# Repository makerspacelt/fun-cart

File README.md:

fun-cart
========

Electric drift cart

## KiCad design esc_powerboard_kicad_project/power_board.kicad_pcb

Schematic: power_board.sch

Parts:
C1, C2, C3, C4, C5, C6, C7, C8, C9, C10, C11, C12, C13, C14, C15, C16, C17, C18, C19, C20: 470u
GS1, GS2, GS3, GS4, GS5, GS6, GS7, GS8, GS9, GS10, GS11, GS12, GS13, GS14, GS15, GS16, GS17, GS18, GS19, GS20: GS2
P1: B+
P2: M-
P3: B-
P4, P5, P6, P7, P8: MOUNT_HOLE
Q1, Q2, Q3, Q4, Q5, Q6, Q7, Q8, Q9, Q10, Q11, Q12, Q13, Q14, Q15, Q16, Q17, Q18, Q19, Q20: IRFB7437PBF; TO220

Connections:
+24V: C1.1, C2.1, C3.1, C4.1, C5.1, C6.1, C7.1, C8.1, C9.1, C10.1, C11.1, C12.1, C13.1, C14.1, C15.1, C16.1, C17.1, C18.1, C19.1, C20.1, GS1.1 (G1), GS2.1 (G1), GS3.1 (G1), GS4.1 (G1), GS5.1 (G1), GS6.1 (G1), GS7.1 (G1), GS8.1 (G1), GS9.1 (G1), GS10.1 (G1), GS11.2 (G2), GS12.2 (G2), GS13.2 (G2), GS14.2 (G2), GS15.2 (G2), GS16.2 (G2), GS17.2 (G2), GS18.2 (G2), GS19.2 (G2), GS20.2 (G2), P1.1, Q1.D, Q3.D, Q5.D, Q7.D, Q9.D, Q11.D, Q13.D, Q15.D, Q17.D, Q19.D
/M-: P2.1, P4.1, P5.1, P6.1, P7.1, P8.1, Q1.S, Q2.D, Q3.S, Q4.D, Q5.S, Q6.D, Q7.S, Q8.D, Q9.S, Q10.D, Q11.S, Q12.D, Q13.S, Q14.D, Q15.S, Q16.D, Q17.S, Q18.D, Q19.S, Q20.D
GND: C1.2, C2.2, C3.2, C4.2, C5.2, C6.2, C7.2, C8.2, C9.2, C10.2, C11.2, C12.2, C13.2, C14.2, C15.2, C16.2, C17.2, C18.2, C19.2, C20.2, GS1.2 (G2), GS2.2 (G2), GS3.2 (G2), GS4.2 (G2), GS5.2 (G2), GS6.2 (G2), GS7.2 (G2), GS8.2 (G2), GS9.2 (G2), GS10.2 (G2), GS11.1 (G1), GS12.1 (G1), GS13.1 (G1), GS14.1 (G1), GS15.1 (G1), GS16.1 (G1), GS17.1 (G1), GS18.1 (G1), GS19.1 (G1), GS20.1 (G1), P3.1, Q2.S, Q4.S, Q6.S, Q8.S, Q10.S, Q12.S, Q14.S, Q16.S, Q18.S, Q20.S

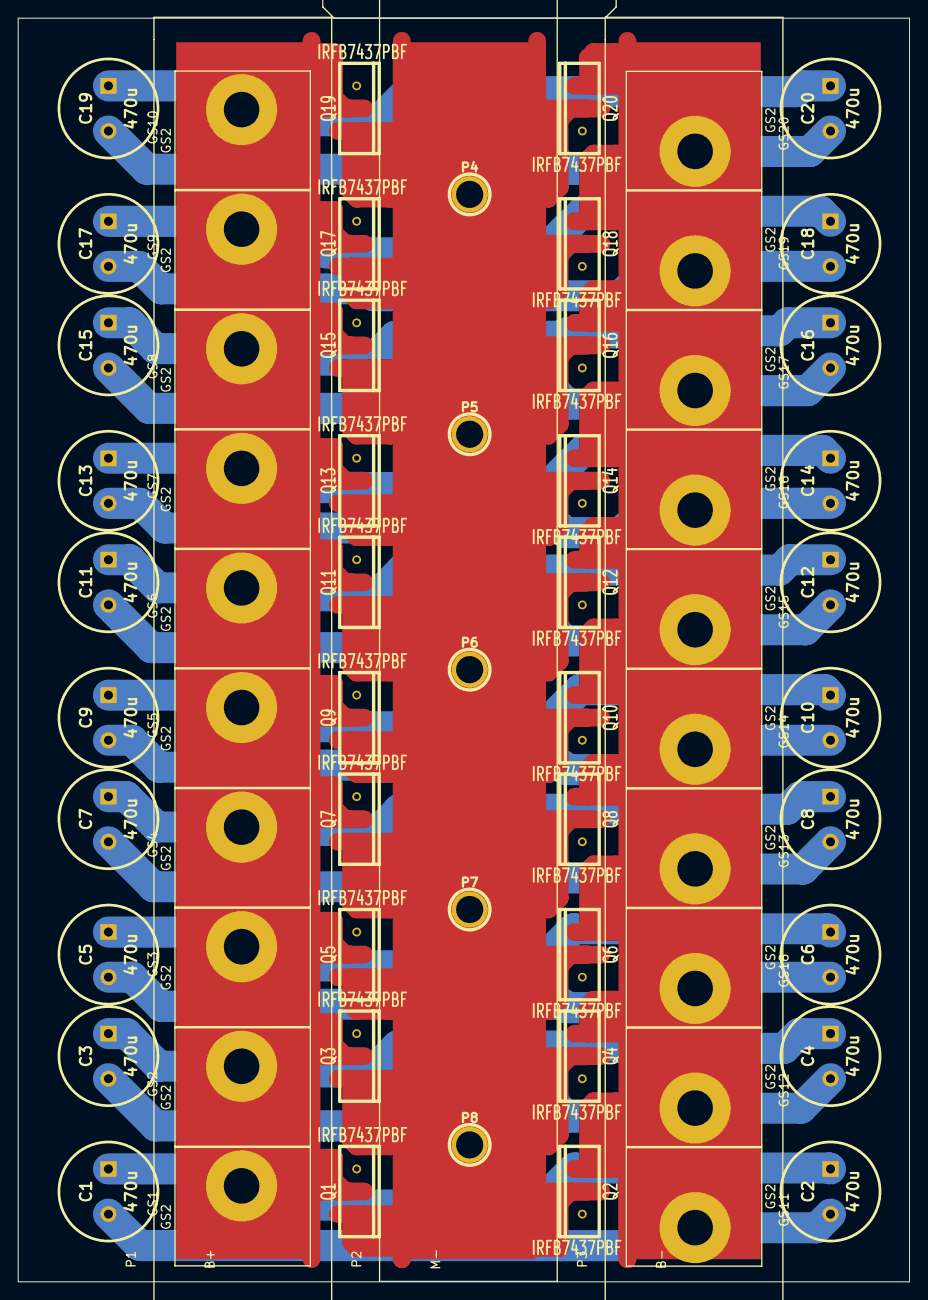
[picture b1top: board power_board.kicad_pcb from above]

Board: 2 copper layers, 100.3 x 142.2 mm, 68 parts (0 on the bottom side), 3 nets.

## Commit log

2015-01-02 adding ESC power board (first prototype)
2015-01-02 adding few kicad generated files to gitignore
2015-01-03 adding origin marker at a corner of pcb
2015-01-03 exporting gerber files
2015-01-11 Changed page size to A4 and positioned pcb to page corner
2015-03-21 fun-cart-control.ino
2015-03-22 removed delay from last 20s counter warning
2015-03-23 fun-cart EEPROM
